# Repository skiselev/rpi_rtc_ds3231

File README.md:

# RPi DS3231 RTC
Maxim DS3231 Based RTC Module for Raspberry Pi

## Introduction
This is a real-time clock (RTC) module for Raspberry Pi and Raspberry Pi Zero. The module is similar to [Adafruit PiRTC](https://www.adafruit.com/product/3386), but uses the highly accurate [Maxim Integrated DS3231](https://www.adafruit.com/product/3386) RTC IC with an integrated temperature-compensated crystal oscillator, and more common CR2032 battery.

## Hardware Documentation

### Schematic and PCB Layout

### Bill of Materials

[RPi DS3231 RTC project on Mouser.com](https://www.mouser.com/ProjectManager/ProjectDetail.aspx?AccessID=eede7ef873) - View and order all components except of the PCB.

[RPi DS3231 RTC on OSH Park](https://oshpark.com/shared_projects/tu7lVnCo) - View and order the PCB.

Component type     | Reference | Description                       | Quantity | Possible sources and notes 
------------------ | --------- | --------------------------------- | -------- | --------------------------
PCB                |           | RPi DS3231 RTC PCB - Version 1.0  | 1        | Order from [OSH Park](https://oshpark.com/shared_projects/tu7lVnCo)
Integrated Circuit | U1        | Maxim DS3231                      | 1        | Mouser [700-DS3231S#T&R-](https://www.mouser.com/ProductDetail/700-DS3231S%23TR-)
Capactior          | C1        | 0.1uF, 0603                       | 6        | Mouser [77-VJ0603Y104JXJPBC](https://www.mouser.com/ProductDetail/77-VJ0603Y104JXJPBC)
Resistor           | R1        | 10 kohm, 0603                     | 1        | Mouser [71-CRCW060310K0FKEB](https://www.mouser.com/ProductDetail/71-CRCW060310K0FKEB)
Connector          | P1        | 3x2, 2.54 mm, socket              | 1        | Mouser [517-929852-01-03-RA](https://www.mouser.com/ProductDetail/517-929852-01-03-RA)
Battery Holder     | BT1       | CR2032 Battery Holder             | 1        | Mouser [712-BAT-HLD-001-THM](https://www.mouser.com/ProductDetail/712-BAT-HLD-001-THM)
Battery            | BT1       | CR2032                            | 1        | Mouser [658-CR2032](https://www.mouser.com/ProductDetail/658-CR2032)

## Software Documentation

### Raspbian Configuration

The following steps assume that you have a fairly new Rapbian distribution installed and running on your Rapsberry Pi, and that RPi DS3231 RTC module is plugged into the Raspberry Pi.

#### Enable I2C Support

Run `raspi-config`:

    $ sudo raspi-config
    
Navigate to the *Interfacing Options* menu. If this menu is missing (on older Raspbian versions), try the *Advanced Options* menu instead.
Next, select the *I2C* menu, and answer *Yes* to *Would you like the ARM I2C interface to be enabled?* and *Would you like the I2C kernel modules to be loaded by default?* questions.

Reboot the system

#### Verify that RTC Module Is Detected

Install `i2c-tools` package:

    $ sudo apt-get install i2c-tools

Run `i2cdetect -y 1` command and verify that the I2C device is detected at address 0x68:

    $ sudo i2cdetect -y 1
         0  1  2  3  4  5  6  7  8  9  a  b  c  d  e  f
    00:          -- -- -- -- -- -- -- -- -- -- -- -- --
    10: -- -- -- -- -- -- -- -- -- -- -- -- -- -- -- --
    20: -- -- -- -- -- -- -- -- -- -- -- -- -- -- -- --
    30: -- -- -- -- -- -- -- -- -- -- -- -- -- -- -- --
    40: -- -- -- -- -- -- -- -- -- -- -- -- -- -- -- --
    50: -- -- -- -- -- -- -- -- -- -- -- -- -- -- -- --
    60: -- -- -- -- -- -- -- -- 68 -- -- -- -- -- -- --
    70: -- -- -- -- -- -- -- --

#### Enable Kernel Support for DS3231 RTC

Open `/boot/firmware/config.txt` in your favorite editor (nano, vi) as root. For example:

    $ sudo nano /boot/firmware/config.txt

Add the following lines at the end of the file:

    # Enable DS3231 RTC
    dtoverlay=i2c-rtc,ds3231

Remove `fake-hwclock` package:

    $ sudo apt-get -y remove fake-hwclock
    $ sudo update-rc.d -f fake-hwclock remove

Enable setting up system time to the RTC time at boot. Open `/lib/udev/hwclock-set` in your favorite editor:

    $ sudo nano /lib/udev/hwclock-set

And comment out the following lines:

    #if [ -e /run/systemd/system ] ; then
    # exit 0
    #fi

Also comment the following line(s):

    #/sbin/hwclock --rtc=$dev --systz --badyear
    #/sbin/hwclock --rtc=$dev --systz

Save the file, and reboot the system

#### Setting and Reading the RTC time from Command Line

* Use `hwclock -w` command to set the RTC time to the system time. You can use `date` command to set and verify the system time prior to writing it to the RTC.
* Use `hwclock --set --date=<date_string>` command to set the RTC time to the time given by <date_string>
* Use `hwclock -r` command to read the time from the RTC

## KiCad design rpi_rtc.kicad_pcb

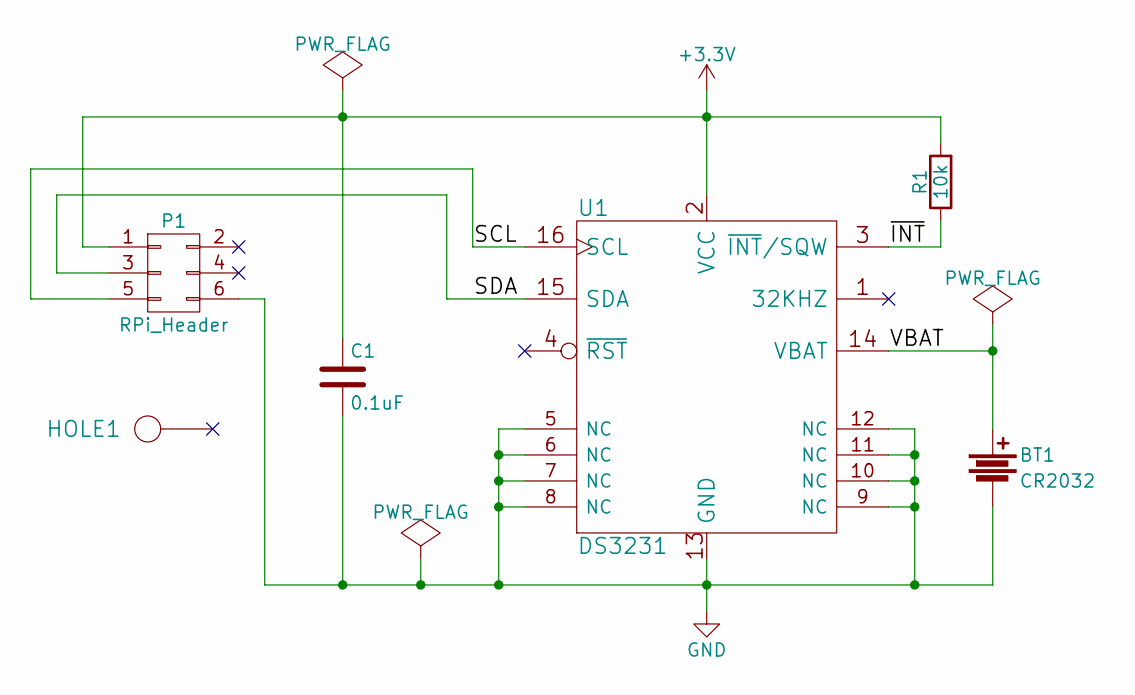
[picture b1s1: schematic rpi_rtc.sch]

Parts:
BT1: CR2032; Battery_Holder_CR2032_THM
C1: 0.1uF; C_0603_HandSoldering
HOLE1: HOLE; Hole_2.75mm
P1: RPi_Header; Conn_Pin_Header_2x3_2.54mm
R1: 10k; R_0603_HandSoldering
U1: DS3231; IC_SOIC16_Wide

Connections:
+3V3: C1.1, P1.1, R1.2, U1.2 (VCC)
/SCL: P1.5, U1.16 (SCL)
/SDA: P1.3, U1.15 (SDA)
/VBAT: BT1.1, U1.14 (VBAT)
/~INT: R1.1, U1.3 (~INT~/SQW)
GND: BT1.2, C1.2, P1.6, U1.5 (NC), U1.6 (NC), U1.7 (NC), U1.8 (NC), U1.9 (NC), U1.10 (NC), U1.11 (NC), U1.12 (NC), U1.13 (GND)

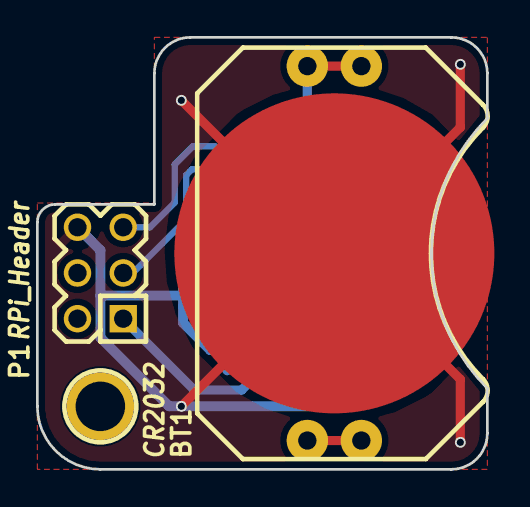
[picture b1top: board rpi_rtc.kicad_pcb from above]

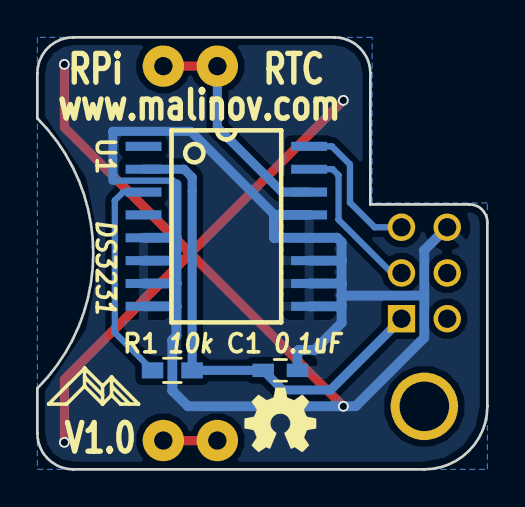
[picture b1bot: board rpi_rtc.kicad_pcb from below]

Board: 2 copper layers, 25.0 x 24.0 mm, 6 parts (3 on the bottom side), 6 nets.

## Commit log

2018-01-28 KiCad: Schematic and PCB, initial commit
2018-01-28 KiCad: move files to the KiCad directory
2018-01-28 Documentation: Add photo, schematic, and datasheet
2018-01-28 README: Add content
2018-01-29 README: Add software configuration notes
2018-01-29 README: Use "RPi DS3231 RTC" as the module name
2025-02-15 Update README.md
    updated location of config.txt
